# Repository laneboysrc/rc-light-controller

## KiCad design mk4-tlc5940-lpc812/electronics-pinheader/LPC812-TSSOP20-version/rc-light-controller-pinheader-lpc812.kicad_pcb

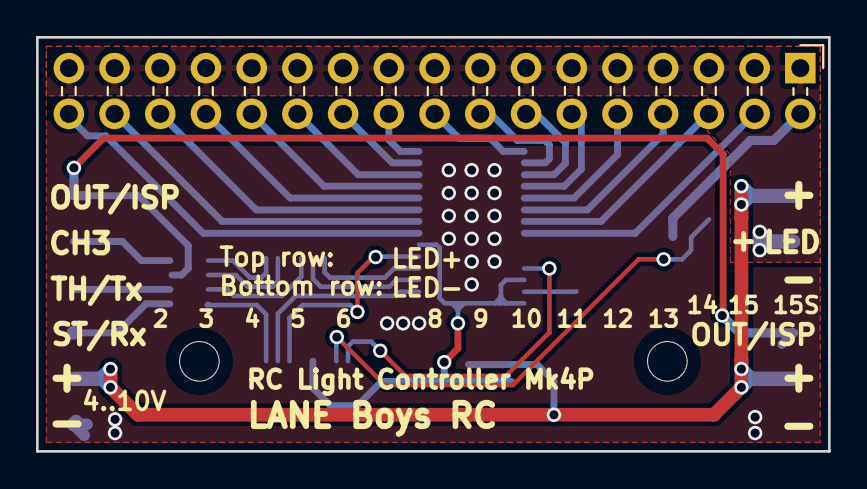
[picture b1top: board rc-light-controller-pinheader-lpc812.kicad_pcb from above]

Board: 2 copper layers, 44.0 x 23.0 mm, 14 parts (0 on the bottom side), 36 nets.

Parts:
C1: 1u/16V; C_0805_2012Metric
C2: 47u/6V3; C_0805_2012Metric
C3: 100n; C_0603_1608Metric
H1, H2: MountingHole; MountingHole_2.2mm_M2_ISO14580
J1: Pinheader right-angle 2x17; PinHeader_2x17_P2.54mm_Horizontal
J2, J3: Pinheader straight 1x06; PinHeader_1x06_P2.54mm_Flat
R1: 2k 1%; R_0603_1608Metric
RN1: 1k x4; R_Array_Convex_4x0603
T9: PMV30UN; SOT-23
U1: LPC812M101JDH20; TSSOP-20_4.4x6.5mm_P0.65mm
U2: TLC5940PWP; SOP65P640X120-29N
U3: MCP1703A-3302_SOT23; SOT-23W

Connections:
+3V3: C2.1, C3.1, U1.15, U2.6, U2.26, U2.28, U3.2
/BLANK: U1.18, U2.2
/CH3: RN1.5, U1.2
/CH3-in: J2.5, RN1.4
/GSCLK: U1.12, U2.25
/LED+: J1.1, J1.3, J1.5, J1.7, J1.9, J1.11, J1.13, J1.15, J1.17, J1.19, J1.21, J1.23, J1.25, J1.27, J1.29, J1.31, J1.33, J3.5
/OUT0: J1.34, U2.7
/OUT1: J1.32, U2.8
/OUT2: J1.30, U2.9
/OUT3: J1.28, U2.10
/OUT4: J1.26, U2.11
/OUT5: J1.24, U2.12
/OUT6: J1.22, U2.13
/OUT7: J1.20, U2.14
/OUT8: J1.18, U2.15
/OUT9: J1.16, U2.16
/OUT10: J1.14, U2.17
/OUT11: J1.12, U2.18
/OUT12: J1.10, U2.19
/OUT13: J1.8, U2.20
/OUT14: J1.6, U2.21
/OUT15: J1.4, U2.22
/OUT15S: T9.1, U1.13
/OUT15S_OUT: J1.2, T9.3
/OUT-ISP: RN1.6, U1.3
/OUT-ISP-out: J2.6, J3.3, RN1.3
/SCLK: U1.7, U2.4
/SIN: U1.17, U2.5
/ST-RX: RN1.8, U1.19
/ST-Rx-in: J2.3, RN1.1
/TH-TX: RN1.7, U1.5
/TH-Tx-in: J2.4, RN1.2
/VIN: C1.1, J2.2, J3.2, J3.6, U3.3
/XLAT: U1.6, U2.3
GND: C1.2, C2.2, C3.2, J2.1, J3.1, J3.4, R1.2, T9.2, U1.16, U2.1, U2.29, U3.1
unnamed: R1.1, U2.27

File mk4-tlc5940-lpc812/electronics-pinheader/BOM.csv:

Reference, Quantity, Value, Footprint, Datasheet
C1 ,1,"1u/16V","Capacitor_SMD:C_0805_2012Metric",""
C2 ,1,"47u/6V3","Capacitor_SMD:C_0805_2012Metric","https://www.vishay.com/doc?40189"
C3 ,1,"100n","Capacitor_SMD:C_0603_1608Metric","~"
H1 H2 ,2,"MountingHole","MountingHole:MountingHole_2.2mm_M2_ISO14580","~"
J1 ,1,"Pinheader right-angle 2x17","Connector_PinHeader_2.54mm:PinHeader_2x17_P2.54mm_Horizontal","~"
J2 J3 ,2,"Pinheader straight 1x06","rc-light-controller-tlc5940-lpc812:PinHeader_1x06_P2.54mm_Flat","~"
R1 ,1,"2k 1%","Resistor_SMD:R_0603_1608Metric","~"
RN1 ,1,"1k x4","Resistor_SMD:R_Array_Convex_4x0603","https://datasheet.lcsc.com/szlcsc/1810311812_UNI-ROYAL-Uniro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"
T9 ,1,"PMV30UN","Package_TO_SOT_SMD:SOT-23","https://assets.nexperia.com/documents/data-sheet/PMV30UN.pdf"
U1 ,1,"LPC812M101JDH20","Package_SO:TSSOP-20_4.4x6.5mm_P0.65mm","http://www.nxp.com/documents/data_sheet/LPC81XM.pdf"
U2 ,1,"TLC5940PWP","rc-light-controller-tlc5940-lpc812:SOP65P640X120-29N","http://www.ti.com/lit/ds/symlink/tlc5940.pdf"
U3 ,1,"MCP1703A-3302_SOT23","Package_TO_SOT_SMD:SOT-23W","http://ww1.microchip.com/downloads/en/DeviceDoc/20005122B.pdf"

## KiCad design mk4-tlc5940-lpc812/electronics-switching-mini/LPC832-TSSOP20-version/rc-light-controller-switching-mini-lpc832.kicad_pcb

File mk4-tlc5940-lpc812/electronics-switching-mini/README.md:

# Mk4S-mini - light controller with pin headers and 3 switching outputs

This is a new variant of the DIY RC Light Controller Mk4.
It has 3 (Mosfet) switched outputs on standard 2.54 mm pin headers.

This light controller is supposed to be used as "Slave" light controller in conjunction with an Mk4, Mk4P or Mk4S light controller. It is useful when more than one switched light output is required when using an Mk4 or Mk4P.

There are two circuit board designs available: one for the NXP LPC812 and one for LPC832 microcontroller, both in TSSOP-20 package.

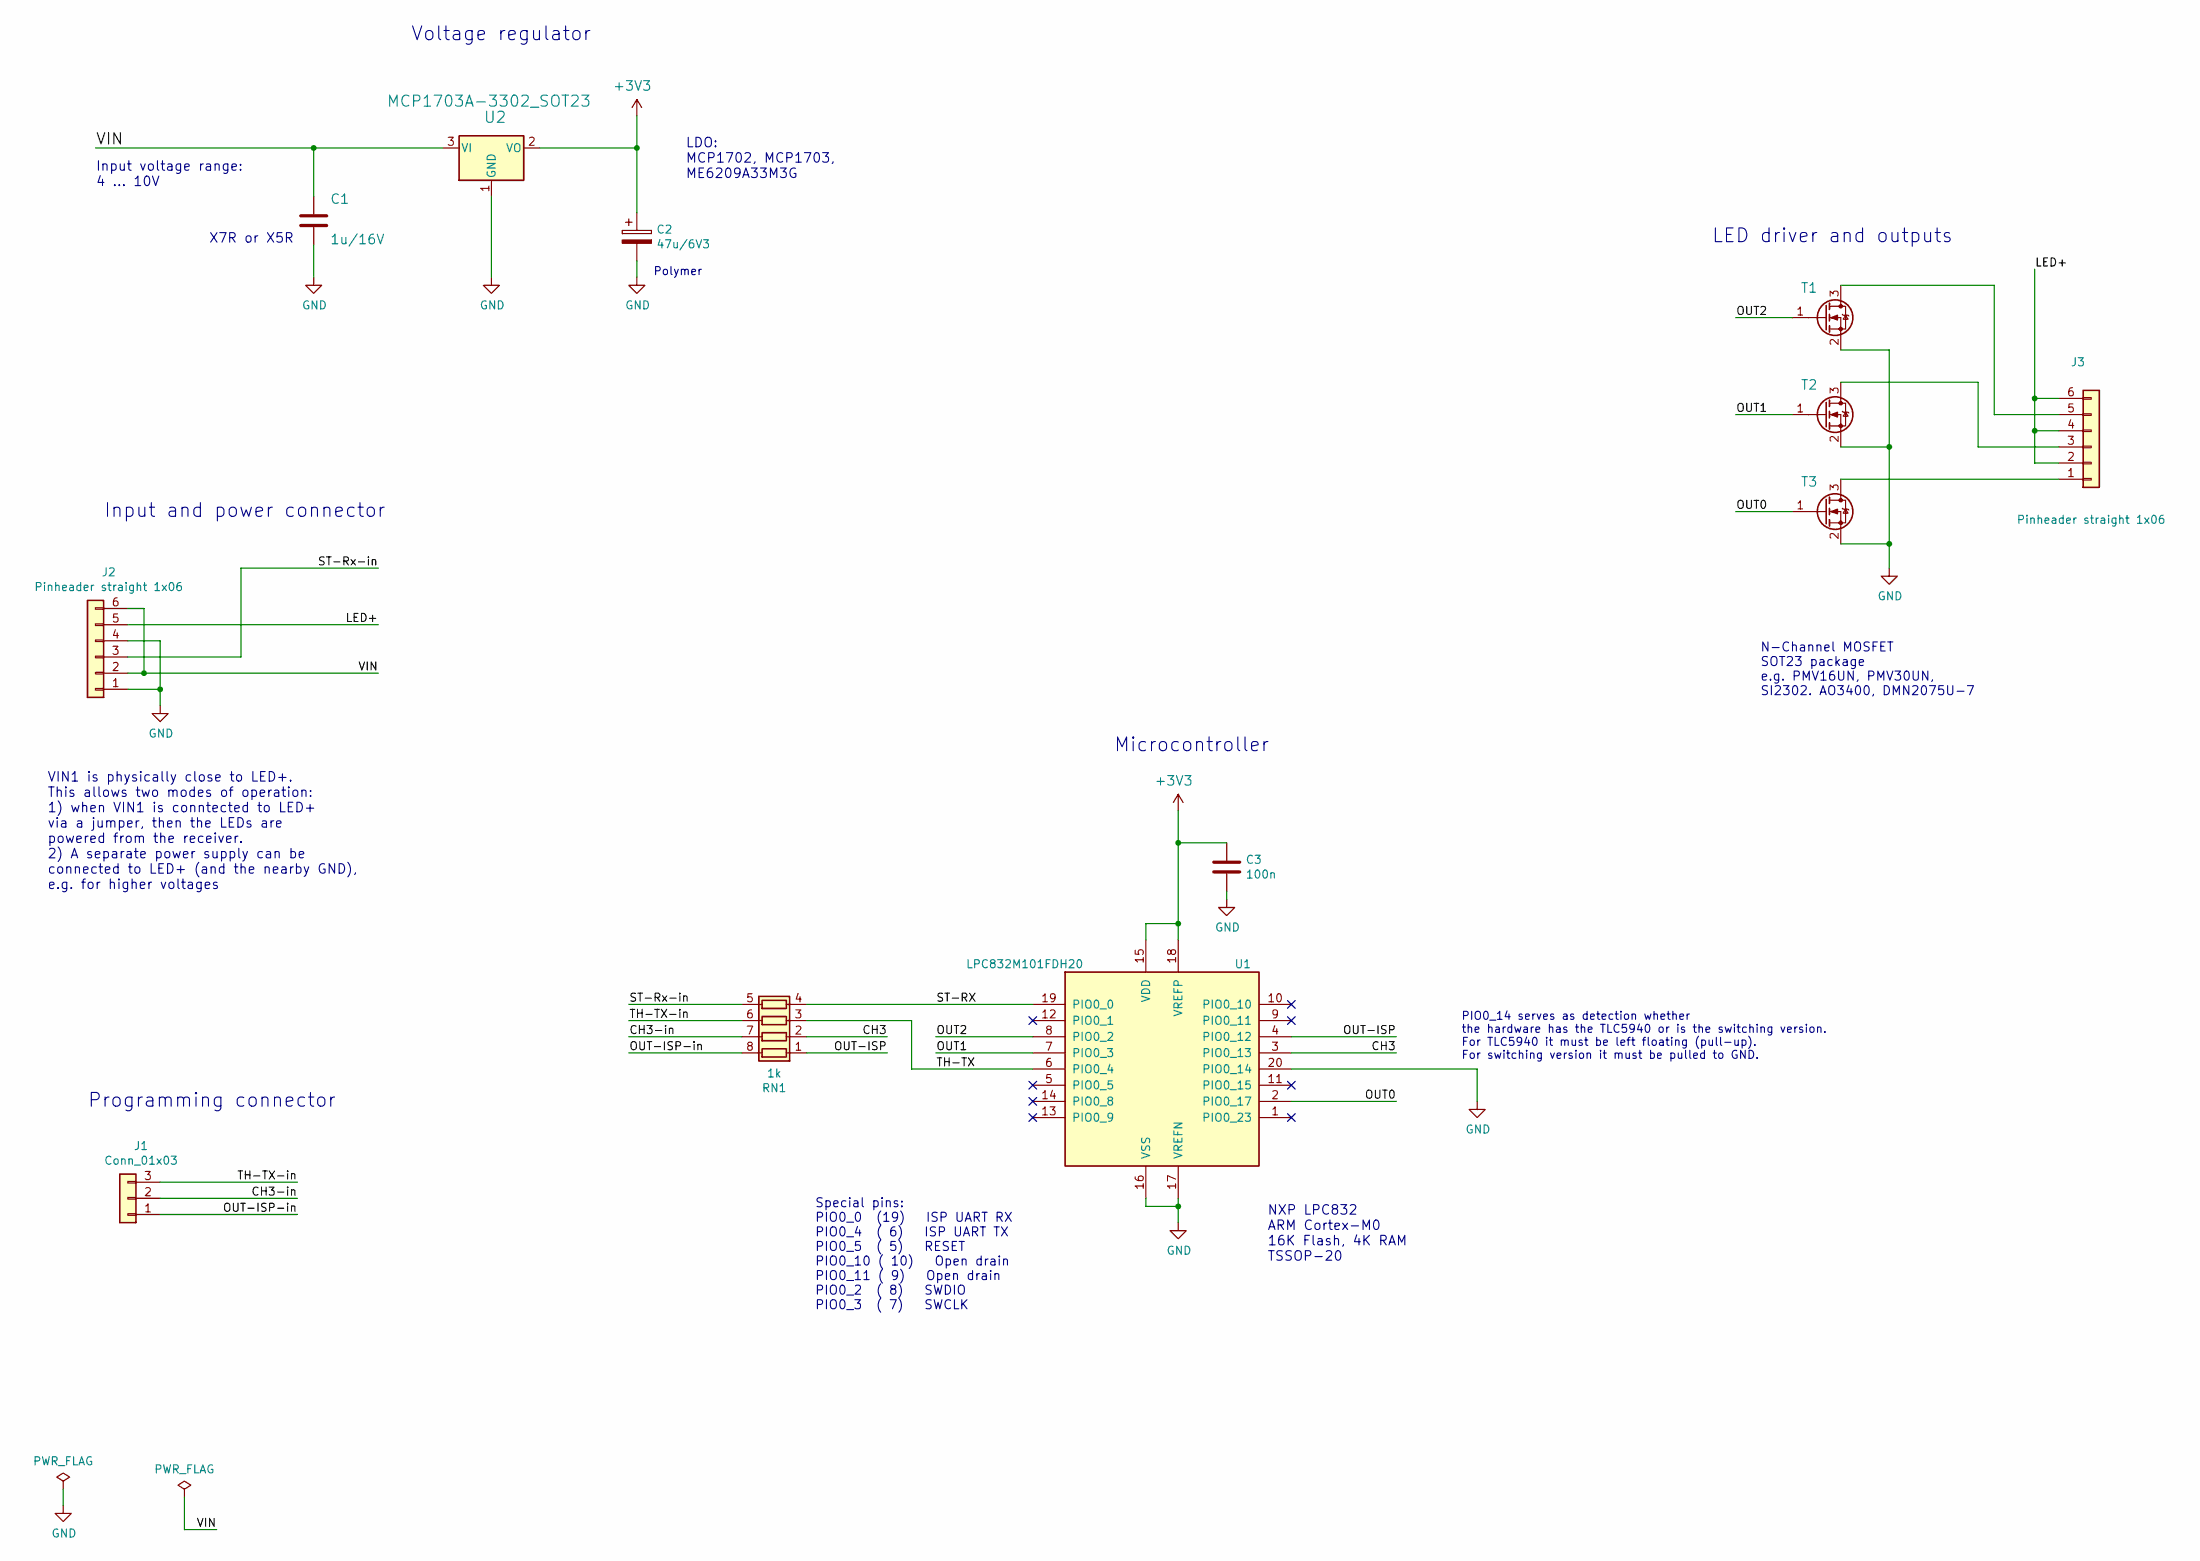
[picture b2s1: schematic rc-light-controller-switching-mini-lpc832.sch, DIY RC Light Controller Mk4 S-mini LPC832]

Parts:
C1: 1u/16V; C_0805_2012Metric
C2: 47u/6V3; C_0805_2012Metric
C3: 100n; C_0603_1608Metric
J1: Conn_01x03; PinHeader_1x03_P2.54mm_Vertical
J2, J3: Pinheader straight 1x06; PinHeader_1x06_P2.54mm_Flat
RN1: 1k; R_Array_Convex_4x0603
T1, T2, T3: PMV30UN; SOT-23
U1: LPC832M101FDH20; TSSOP-20_4.4x6.5mm_P0.65mm
U2: MCP1703A-3302_SOT23; SOT-23W

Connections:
+3V3: C2.1, C3.1, U1.15 (VDD), U1.18 (VREFP), U2.2 (VO)
/CH3: RN1.2 (R2.1), U1.3 (PIO0_13)
/CH3-in: J1.2, RN1.7 (R2.2)
/LED+: J2.5, J3.2, J3.4, J3.6
/OUT0: T3.1 (G), U1.2 (PIO0_17)
/OUT1: T2.1 (G), U1.7 (PIO0_3)
/OUT2: T1.1 (G), U1.8 (PIO0_2)
/OUT-ISP: RN1.1 (R1.1), U1.4 (PIO0_12)
/OUT-ISP-in: J1.1, RN1.8 (R1.2)
/ST-RX: RN1.4 (R4.1), U1.19 (PIO0_0)
/ST-Rx-in: J2.3, RN1.5 (R4.2)
/TH-TX: RN1.3 (R3.1), U1.6 (PIO0_4)
/TH-TX-in: J1.3, RN1.6 (R3.2)
/VIN: C1.1, J2.2, J2.6, U2.3 (VI)
GND: C1.2, C2.2, C3.2, J2.1, J2.4, T1.2 (S), T2.2 (S), T3.2 (S), U1.16 (VSS), U1.17 (VREFN), U1.20 (PIO0_14), U2.1 (GND)
unnamed: J3.1, T3.3 (D)
unnamed: J3.3, T2.3 (D)
unnamed: J3.5, T1.3 (D)

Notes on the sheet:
Special pins: PIO0_0 (19) ISP UART RX PIO0_4 ( 6) ISP UART TX PIO0_5 ( 5) RESET PIO0_10 ( 10) Open drain PIO0_11 ( 9) Open drain PIO0_2 ( 8) SWDIO PIO0_3 ( 7) SWCLK
Input and power connector
Voltage regulator
Microcontroller
X7R or X5R
Input voltage range: 4 ... 10V
LDO: MCP1702, MCP1703, ME6209A33M3G
N-Channel MOSFET SOT23 package e.g. PMV16UN, PMV30UN, SI2302. AO3400, DMN2075U-7
Polymer
LED driver and outputs
VIN1 is physically close to LED+. This allows two modes of operation: 1) when VIN1 is conntected to LED+ via a jumper, then the LEDs are powered from the receiver. 2) A separate power supply can be connected to LED+ (and the nearby GND), e.g. for higher voltages
PIO0_14 serves as detection whether the hardware has the TLC5940 or is the switching version. For TLC5940 it must be left floating (pull-up). For switching version it must be pulled to GND.
Programming connector
NXP LPC832 ARM Cortex-M0 16K Flash, 4K RAM TSSOP-20

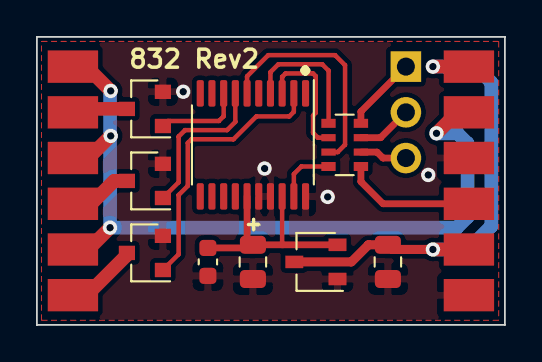
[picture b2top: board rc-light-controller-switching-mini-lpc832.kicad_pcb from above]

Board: 2 copper layers, 26.0 x 16.0 mm, 12 parts (0 on the bottom side), 18 nets.

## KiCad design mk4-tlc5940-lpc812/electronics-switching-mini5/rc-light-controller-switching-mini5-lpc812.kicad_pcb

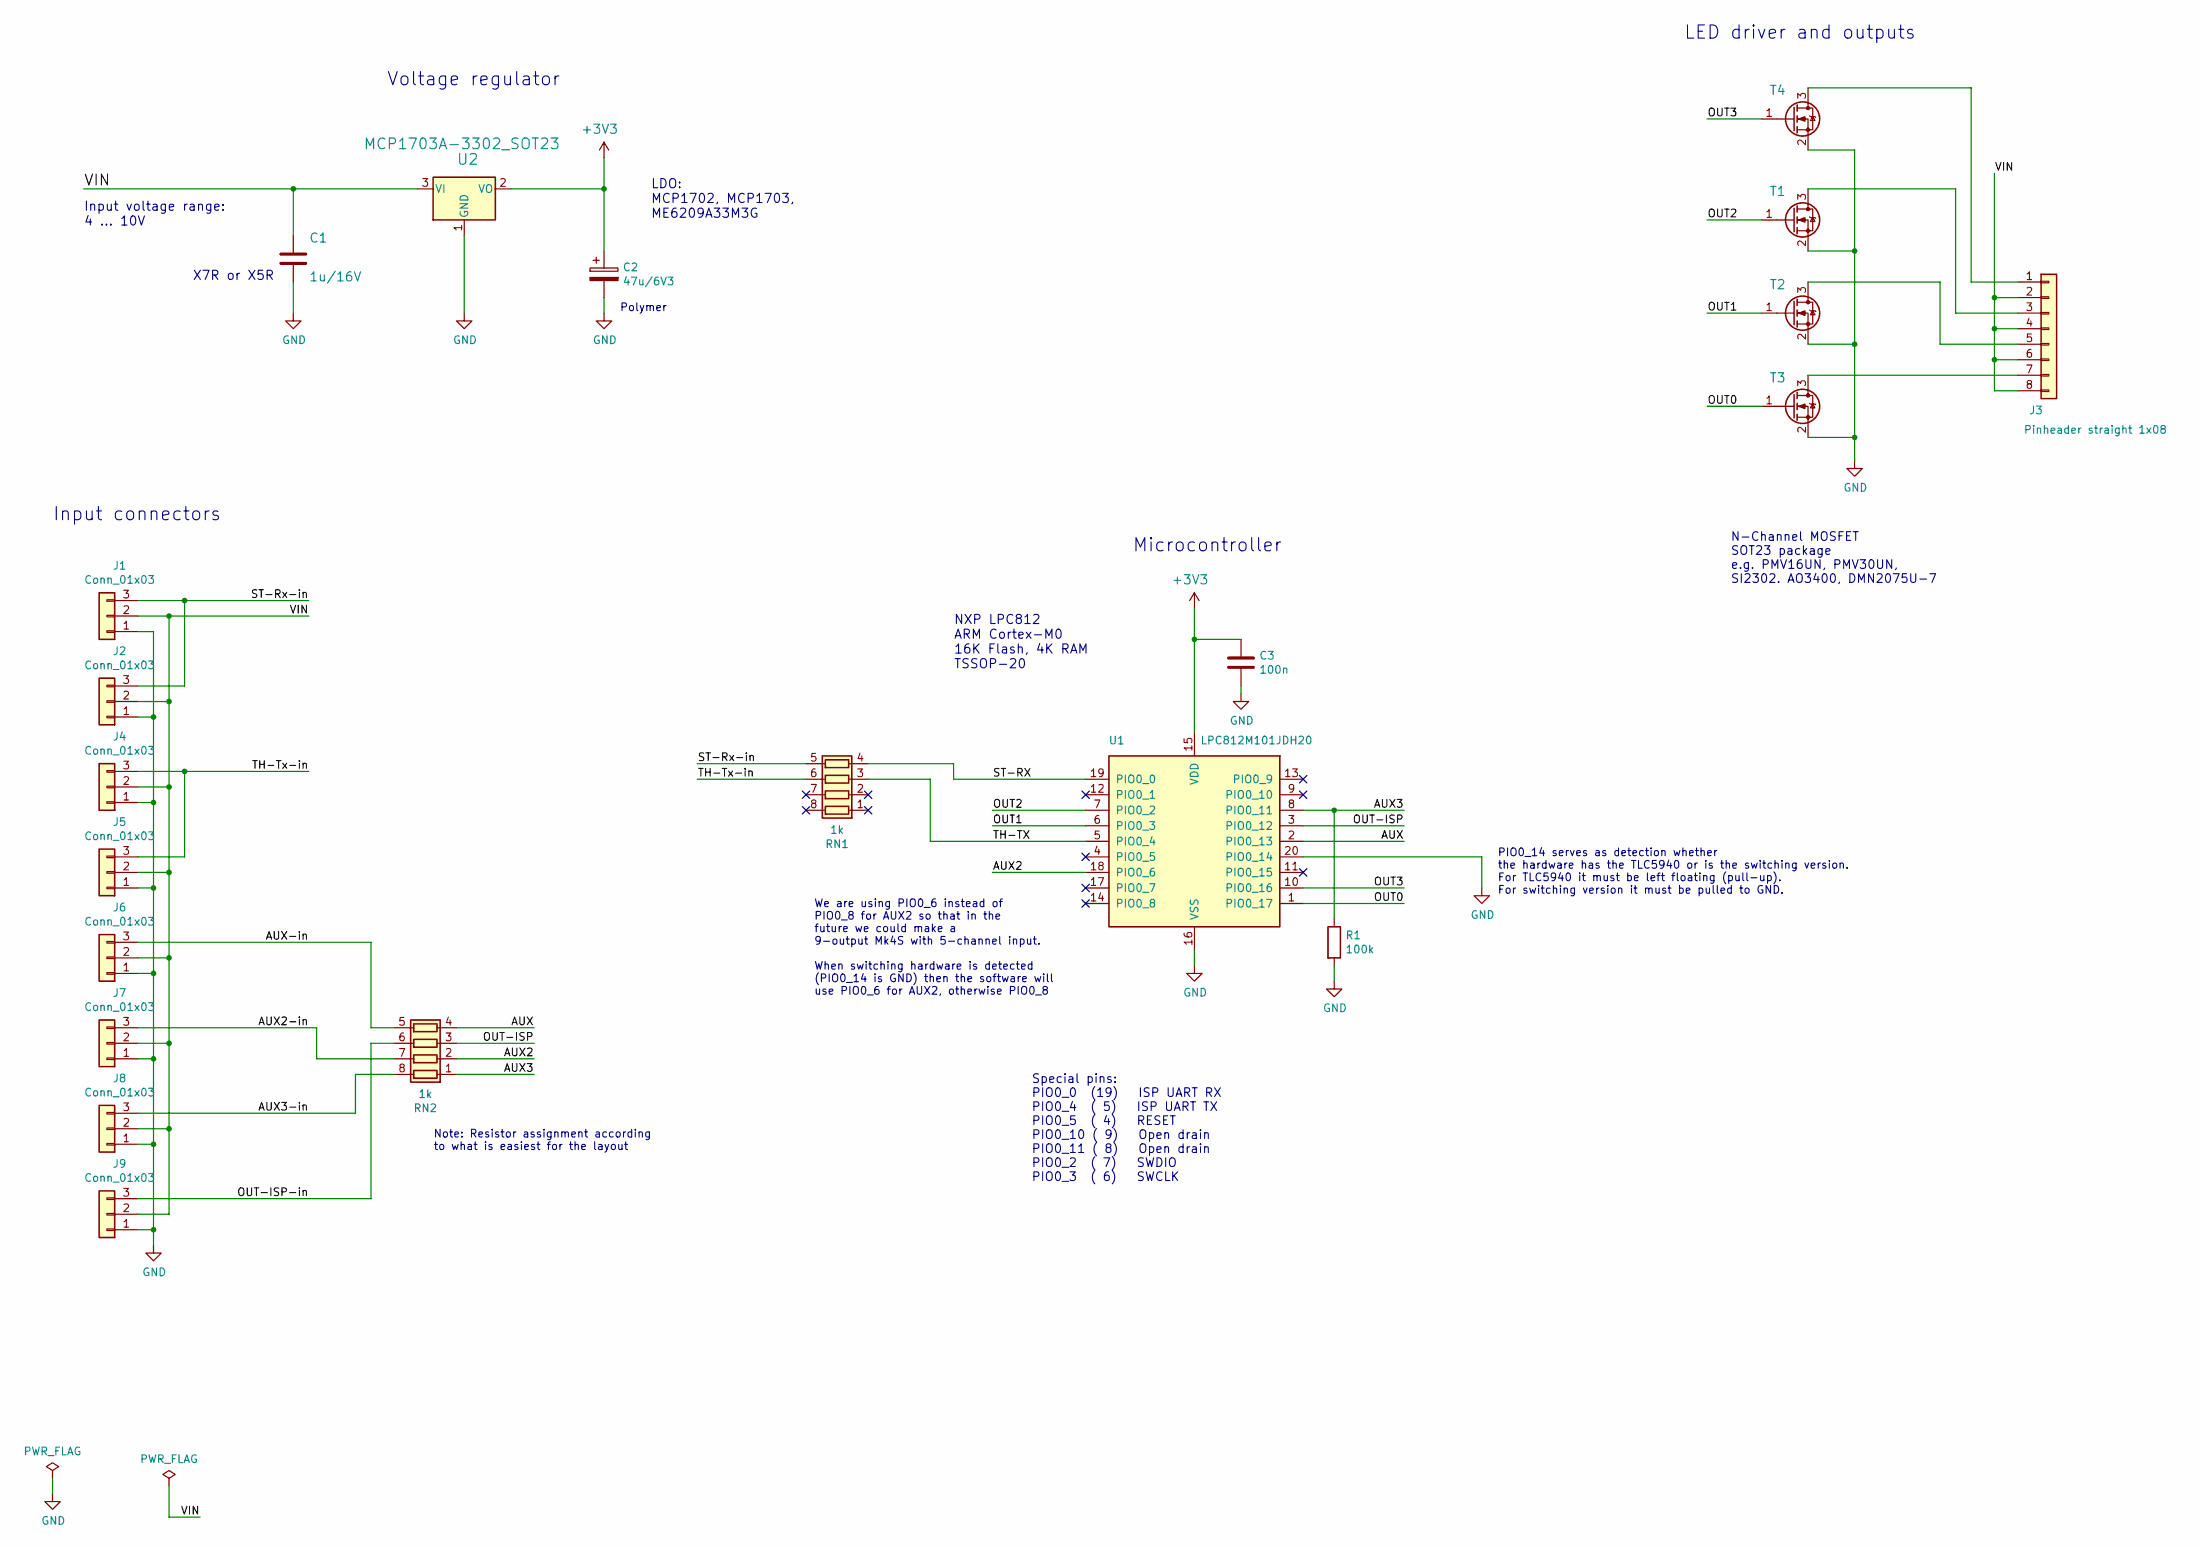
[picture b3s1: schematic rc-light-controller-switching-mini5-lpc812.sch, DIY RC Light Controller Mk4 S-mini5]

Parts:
C1: 1u/16V; C_0805_2012Metric
C2: 47u/6V3; C_0805_2012Metric
C3: 100n; C_0603_1608Metric
J1, J2, J4, J5, J6, J7, J8, J9: Conn_01x03; PinHeader_1x03_P2.54mm_Vertical_nosilk
J3: Pinheader straight 1x08; PinHeader_1x08_P2.54mm_Vertical_nosilk
R1: 100k; R_0603_1608Metric
RN1, RN2: 1k; R_Array_Convex_4x0603
T1, T2, T3, T4: PMV30UN; SOT-23
U1: LPC812M101JDH20; TSSOP-20_4.4x6.5mm_P0.65mm
U2: MCP1703A-3302_SOT23; SOT-23W

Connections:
+3V3: C2.1, C3.1, U1.15 (VDD), U2.2 (VO)
/AUX: RN2.4 (R4.1), U1.2 (PIO0_13)
/AUX2: RN2.2 (R2.1), U1.18 (PIO0_6)
/AUX2-in: J7.3, RN2.7 (R2.2)
/AUX3: R1.1, RN2.1 (R1.1), U1.8 (PIO0_11)
/AUX3-in: J8.3, RN2.8 (R1.2)
/AUX-in: J6.3, RN2.5 (R4.2)
/OUT0: T3.1 (G), U1.1 (PIO0_17)
/OUT1: T2.1 (G), U1.6 (PIO0_3)
/OUT2: T1.1 (G), U1.7 (PIO0_2)
/OUT3: T4.1 (G), U1.10 (PIO0_16)
/OUT-ISP: RN2.3 (R3.1), U1.3 (PIO0_12)
/OUT-ISP-in: J9.3, RN2.6 (R3.2)
/ST-RX: RN1.4 (R4.1), U1.19 (PIO0_0)
/ST-Rx-in: J1.3, J2.3, RN1.5 (R4.2)
/TH-TX: RN1.3 (R3.1), U1.5 (PIO0_4)
/TH-Tx-in: J4.3, J5.3, RN1.6 (R3.2)
/VIN: C1.1, J1.2, J2.2, J3.2, J3.4, J3.6, J3.8, J4.2, J5.2, J6.2, J7.2, J8.2, J9.2, U2.3 (VI)
GND: C1.2, C2.2, C3.2, J1.1, J2.1, J4.1, J5.1, J6.1, J7.1, J8.1, J9.1, R1.2, T1.2 (S), T2.2 (S), T3.2 (S), T4.2 (S), U1.16 (VSS), U1.20 (PIO0_14), U2.1 (GND)
unnamed: J3.1, T4.3 (D)
unnamed: J3.3, T1.3 (D)
unnamed: J3.5, T2.3 (D)
unnamed: J3.7, T3.3 (D)

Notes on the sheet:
Special pins: PIO0_0 (19) ISP UART RX PIO0_4 ( 5) ISP UART TX PIO0_5 ( 4) RESET PIO0_10 ( 9) Open drain PIO0_11 ( 8) Open drain PIO0_2 ( 7) SWDIO PIO0_3 ( 6) SWCLK
Input connectors
Voltage regulator
Microcontroller
X7R or X5R
Input voltage range: 4 ... 10V
LDO: MCP1702, MCP1703, ME6209A33M3G
NXP LPC812 ARM Cortex-M0 16K Flash, 4K RAM TSSOP-20
N-Channel MOSFET SOT23 package e.g. PMV16UN, PMV30UN, SI2302. AO3400, DMN2075U-7
Polymer
LED driver and outputs
PIO0_14 serves as detection whether the hardware has the TLC5940 or is the switching version. For TLC5940 it must be left floating (pull-up). For switching version it must be pulled to GND.
We are using PIO0_6 instead of PIO0_8 for AUX2 so that in the future we could make a 9-output Mk4S with 5-channel input. When switching hardware is detected (PIO0_14 is GND) then the software will use PIO0_6 for AUX2, otherwise PIO0_8
Note: Resistor assignment according to what is easiest for the layout

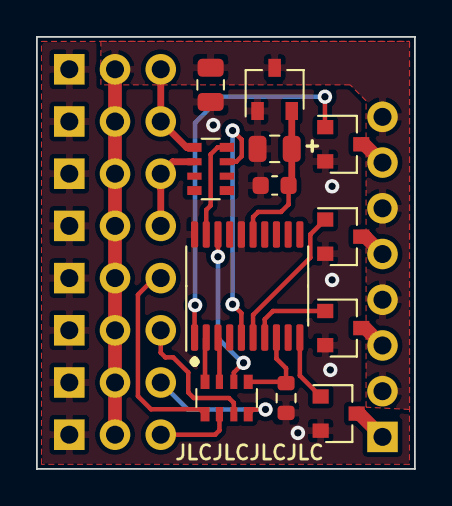
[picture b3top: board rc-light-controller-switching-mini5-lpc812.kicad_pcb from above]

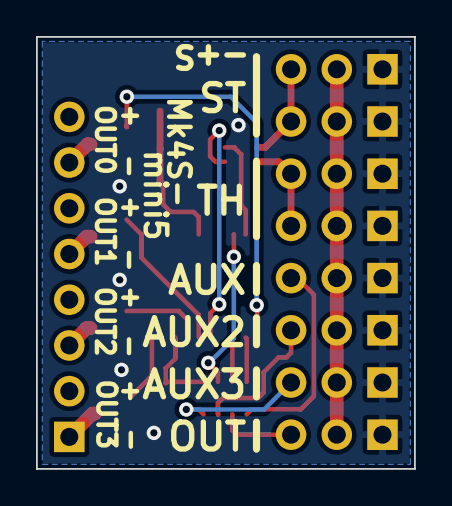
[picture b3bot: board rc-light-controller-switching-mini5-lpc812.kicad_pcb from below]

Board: 2 copper layers, 21.0 x 24.0 mm, 21 parts (9 on the bottom side), 23 nets.

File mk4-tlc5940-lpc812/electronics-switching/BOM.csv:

Reference, Quantity, Value, Footprint, Datasheet
C1 ,1,"1u/16V","Capacitor_SMD:C_0805_2012Metric",""
C2 ,1,"47u/6V3","Capacitor_SMD:C_0805_2012Metric","https://www.vishay.com/doc?40189"
C3 ,1,"100n","Capacitor_SMD:C_0603_1608Metric","~"
H1 H2 ,2,"MountingHole","MountingHole:MountingHole_2.2mm_M2_ISO14580","~"
J1 ,1,"Pinheader right-angle 2x17","Connector_PinHeader_2.54mm:PinHeader_2x17_P2.54mm_Horizontal","~"
J2 J3 ,2,"Pinheader straight 1x06","rc-light-controller-tlc5940-lpc812:PinHeader_1x06_P2.54mm_Flat","~"
RN1 ,1,"1k x4","Resistor_SMD:R_Array_Convex_4x0603","https://datasheet.lcsc.com/szlcsc/1810311812_UNI-ROYAL-Uniro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"
T1 T2 T3 T4 T5 T6 T7 T9 T8 ,9,"PMV30UN","Package_TO_SOT_SMD:SOT-23","https://assets.nexperia.com/documents/data-sheet/PMV30UN.pdf"
U1 ,1,"LPC812M101JDH20","Package_SO:TSSOP-20_4.4x6.5mm_P0.65mm","http://www.nxp.com/documents/data_sheet/LPC81XM.pdf"
U2 ,1,"3V3","Package_TO_SOT_SMD:SOT-23W",""

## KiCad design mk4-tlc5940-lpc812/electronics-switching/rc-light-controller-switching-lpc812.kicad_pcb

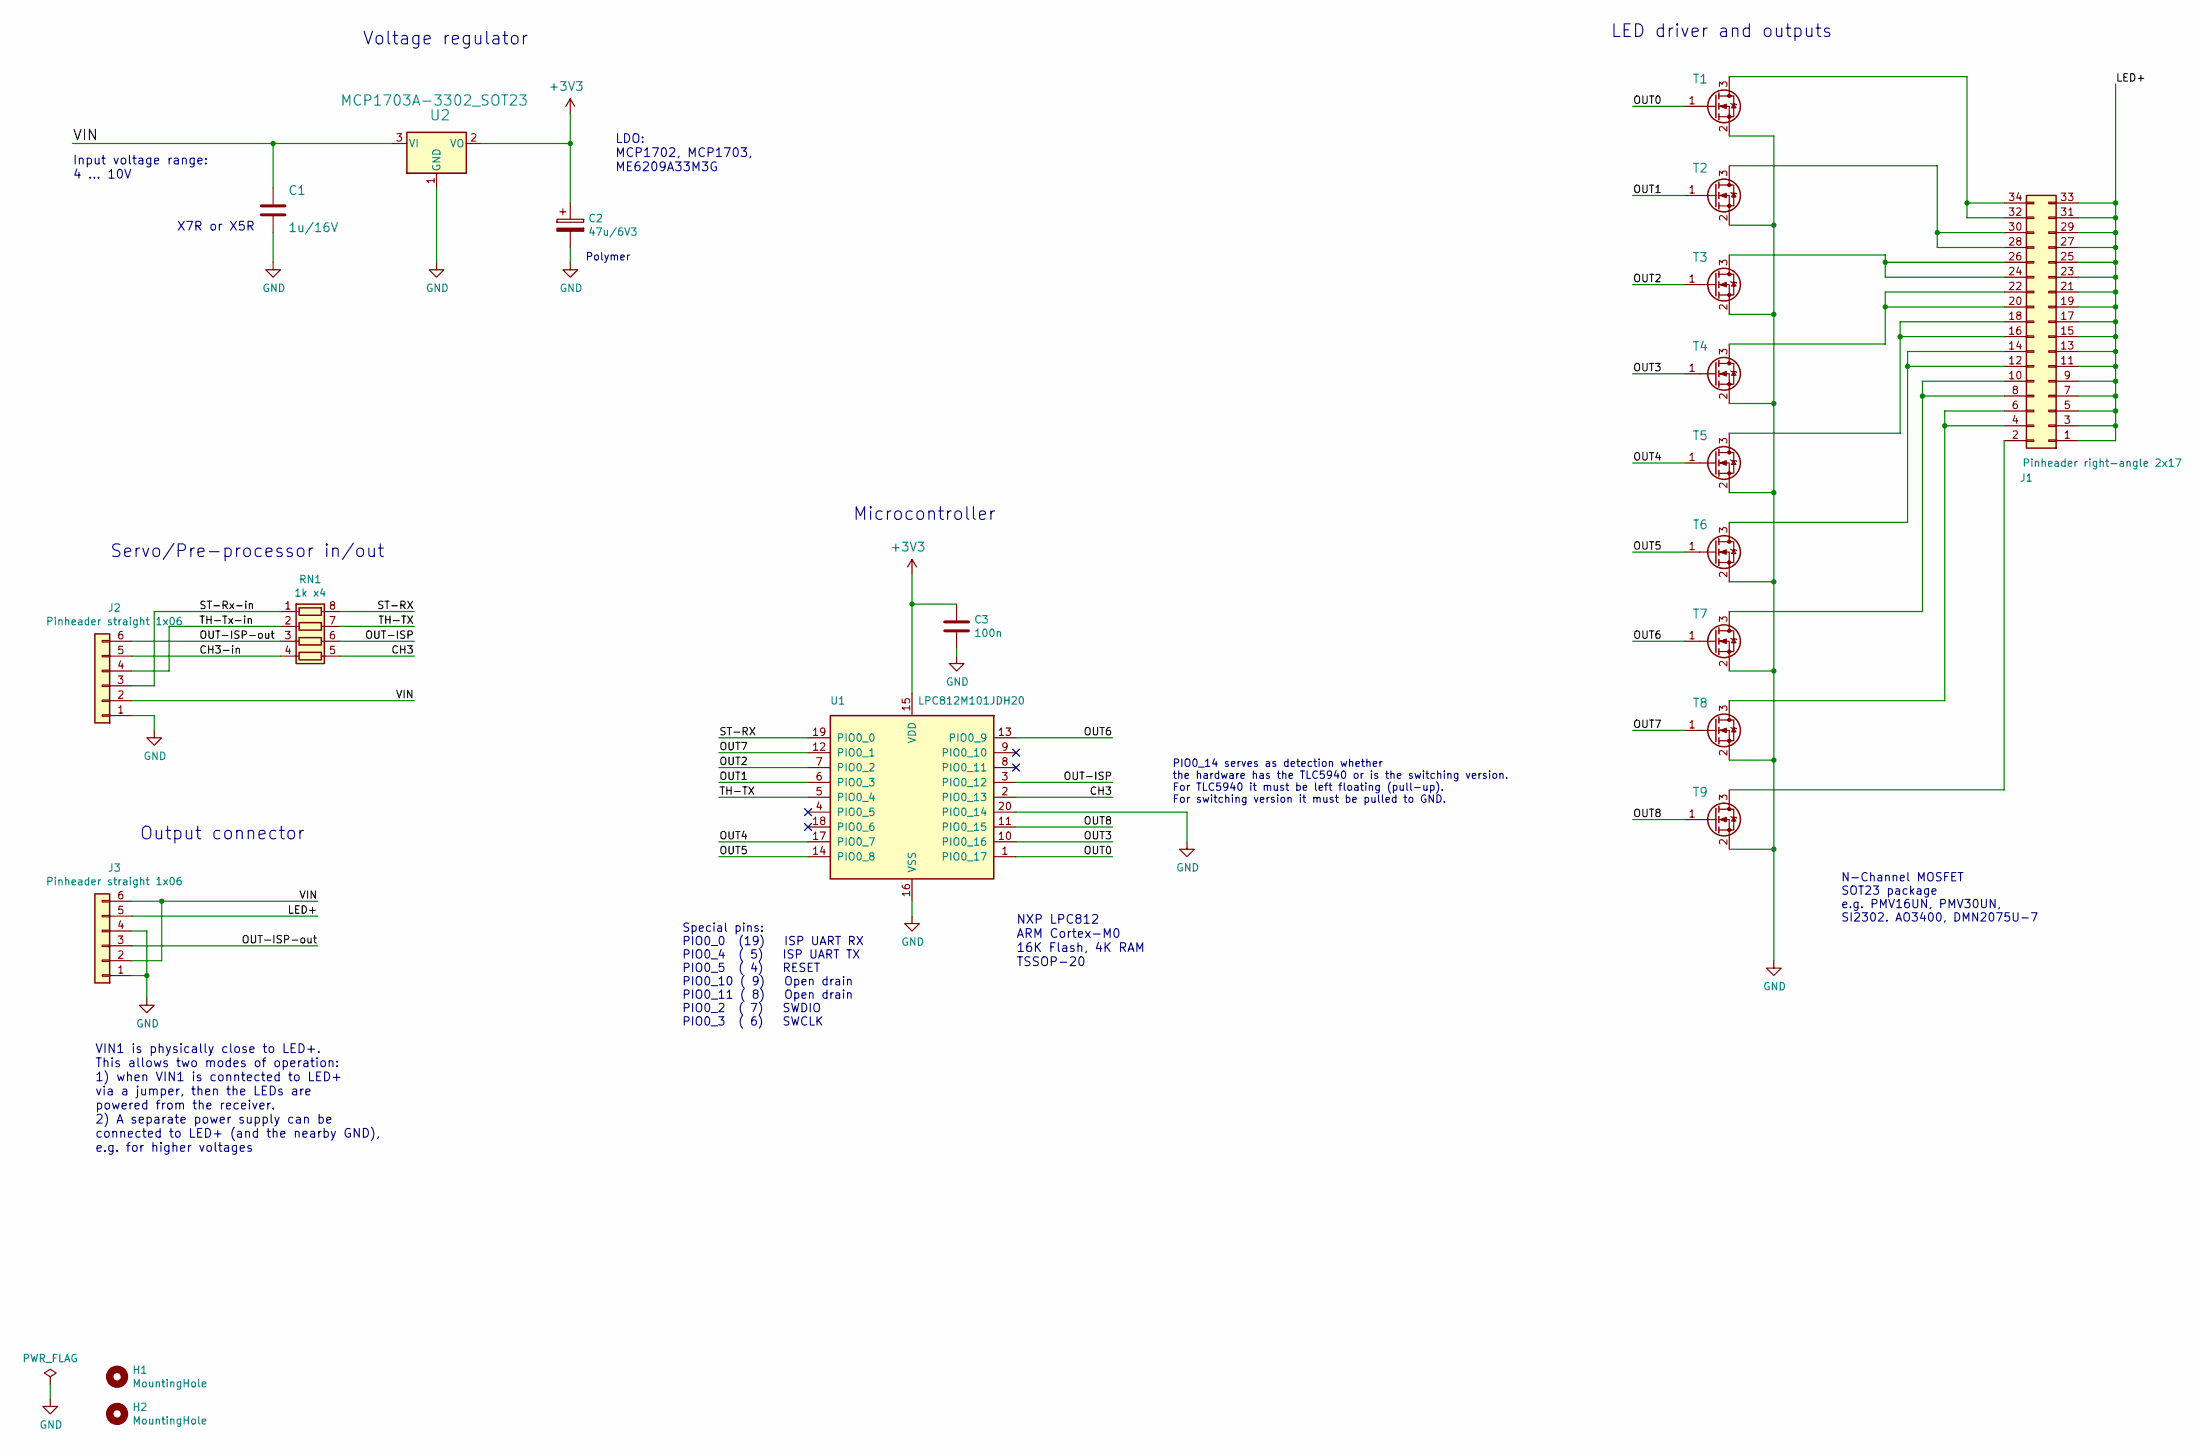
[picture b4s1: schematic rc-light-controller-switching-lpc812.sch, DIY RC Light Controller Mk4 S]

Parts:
C1: 1u/16V; C_0805_2012Metric
C2: 47u/6V3; C_0805_2012Metric
C3: 100n; C_0603_1608Metric
H1, H2: MountingHole; MountingHole_2.2mm_M2_ISO14580
J1: Pinheader right-angle 2x17; PinHeader_2x17_P2.54mm_Horizontal
J2, J3: Pinheader straight 1x06; PinHeader_1x06_P2.54mm_Flat
RN1: 1k x4; R_Array_Convex_4x0603
T1, T2, T3, T4, T5, T6, T7, T8, T9: PMV30UN; SOT-23
U1: LPC812M101JDH20; TSSOP-20_4.4x6.5mm_P0.65mm
U2: MCP1703A-3302_SOT23; SOT-23W

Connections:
+3V3: C2.1, C3.1, U1.15 (VDD), U2.2 (VO)
/CH3: RN1.5 (R4.2), U1.2 (PIO0_13)
/CH3-in: J2.5, RN1.4 (R4.1)
/LED+: J1.1, J1.3, J1.5, J1.7, J1.9, J1.11, J1.13, J1.15, J1.17, J1.19, J1.21, J1.23, J1.25, J1.27, J1.29, J1.31, J1.33, J3.5
/OUT0: T1.1 (G), U1.1 (PIO0_17)
/OUT1: T2.1 (G), U1.6 (PIO0_3)
/OUT2: T3.1 (G), U1.7 (PIO0_2)
/OUT3: T4.1 (G), U1.10 (PIO0_16)
/OUT4: T5.1 (G), U1.17 (PIO0_7)
/OUT5: T6.1 (G), U1.14 (PIO0_8)
/OUT6: T7.1 (G), U1.13 (PIO0_9)
/OUT7: T8.1 (G), U1.12 (PIO0_1)
/OUT15S: T9.1 (G), U1.11 (PIO0_15)
/OUT-ISP: RN1.6 (R3.2), U1.3 (PIO0_12)
/OUT-ISP-out: J2.6, J3.3, RN1.3 (R3.1)
/ST-RX: RN1.8 (R1.2), U1.19 (PIO0_0)
/ST-Rx-in: J2.3, RN1.1 (R1.1)
/TH-TX: RN1.7 (R2.2), U1.5 (PIO0_4)
/TH-Tx-in: J2.4, RN1.2 (R2.1)
/VIN: C1.1, J2.2, J3.2, J3.6, U2.3 (VI)
GND: C1.2, C2.2, C3.2, J2.1, J3.1, J3.4, T1.2 (S), T2.2 (S), T3.2 (S), T4.2 (S), T5.2 (S), T6.2 (S), T7.2 (S), T8.2 (S), T9.2 (S), U1.16 (VSS), U1.20 (PIO0_14), U2.1 (GND)
unnamed: J1.2, T9.3 (D)
unnamed: J1.4, J1.6, T8.3 (D)
unnamed: J1.8, J1.10, T7.3 (D)
unnamed: J1.12, J1.14, T6.3 (D)
unnamed: J1.16, J1.18, T5.3 (D)
unnamed: J1.20, J1.22, T4.3 (D)
unnamed: J1.24, J1.26, T3.3 (D)
unnamed: J1.28, J1.30, T2.3 (D)
unnamed: J1.32, J1.34, T1.3 (D)

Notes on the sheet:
Special pins: PIO0_0 (19) ISP UART RX PIO0_4 ( 5) ISP UART TX PIO0_5 ( 4) RESET PIO0_10 ( 9) Open drain PIO0_11 ( 8) Open drain PIO0_2 ( 7) SWDIO PIO0_3 ( 6) SWCLK
Servo/Pre-processor in/out
Voltage regulator
Microcontroller
X7R or X5R
Input voltage range: 4 ... 10V
LDO: MCP1702, MCP1703, ME6209A33M3G
NXP LPC812 ARM Cortex-M0 16K Flash, 4K RAM TSSOP-20
N-Channel MOSFET SOT23 package e.g. PMV16UN, PMV30UN, SI2302. AO3400, DMN2075U-7
Polymer
LED driver and outputs
VIN1 is physically close to LED+. This allows two modes of operation: 1) when VIN1 is conntected to LED+ via a jumper, then the LEDs are powered from the receiver. 2) A separate power supply can be connected to LED+ (and the nearby GND), e.g. for higher voltages
Output connector
PIO0_14 serves as detection whether the hardware has the TLC5940 or is the switching version. For TLC5940 it must be left floating (pull-up). For switching version it must be pulled to GND.

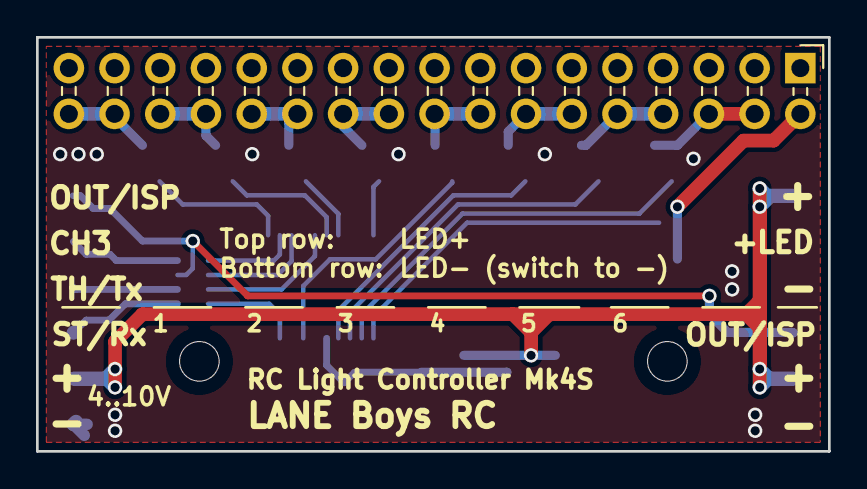
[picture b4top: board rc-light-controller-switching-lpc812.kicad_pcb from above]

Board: 2 copper layers, 44.0 x 23.0 mm, 20 parts (0 on the bottom side), 30 nets.

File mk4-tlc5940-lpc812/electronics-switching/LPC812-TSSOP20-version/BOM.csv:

Reference, Quantity, Value, Footprint, Datasheet
C1 ,1,"1u/16V","Capacitor_SMD:C_0805_2012Metric",""
C2 ,1,"47u/6V3","Capacitor_SMD:C_0805_2012Metric","https://www.vishay.com/doc?40189"
C3 ,1,"100n","Capacitor_SMD:C_0603_1608Metric","~"
H1 H2 ,2,"MountingHole","MountingHole:MountingHole_2.2mm_M2_ISO14580","~"
J1 ,1,"Pinheader right-angle 2x17","Connector_PinHeader_2.54mm:PinHeader_2x17_P2.54mm_Horizontal","~"
J2 J3 ,2,"Pinheader straight 1x06","rc-light-controller-tlc5940-lpc812:PinHeader_1x06_P2.54mm_Flat","~"
RN1 ,1,"1k x4","Resistor_SMD:R_Array_Convex_4x0603","https://datasheet.lcsc.com/szlcsc/1810311812_UNI-ROYAL-Uniro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"
T1 T2 T3 T4 T5 T6 T7 T9 T8 ,9,"PMV30UN","Package_TO_SOT_SMD:SOT-23","https://assets.nexperia.com/documents/data-sheet/PMV30UN.pdf"
U1 ,1,"LPC812M101JDH20","Package_SO:TSSOP-20_4.4x6.5mm_P0.65mm","http://www.nxp.com/documents/data_sheet/LPC81XM.pdf"
U2 ,1,"MCP1703A-3302","Package_TO_SOT_SMD:SOT-23W",""

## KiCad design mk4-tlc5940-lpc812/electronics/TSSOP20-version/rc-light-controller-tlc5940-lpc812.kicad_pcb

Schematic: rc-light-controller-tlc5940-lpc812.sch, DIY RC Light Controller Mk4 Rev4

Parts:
C1: 1u/16V; C_0805_2012Metric
C2: 47u/6V3; C_0805_2012Metric
C3: 100n; C_0603_1608Metric
LED+1, LED+2: SMD50X100
OUT0, OUT1, OUT2, OUT3, OUT4, OUT5, OUT6, OUT7, OUT8, OUT9, OUT10, OUT11, OUT12, OUT13, OUT14, OUT15, OUT15S1: SMD50X100
PAD1: +; SMD80X120
PAD2: -; SMD80X120
PAD3: ST/Rx; SMD80X120
PAD4: TH/Tx; SMD80X120
PAD5: CH3; SMD80X120
PAD6: OUT/ISP; SMD80X120
R1: 2k0=20mA; R_0603_1608Metric
R2, R3, R4, R5: 1k; R_0603_1608Metric
T1: NMOSSOT23; SOT-23
U1: 3V3; SOT-23W
U2: LPC812M101JDH20; TSSOP-20_4.4x6.5mm_P0.65mm
U3: TLC5940PWP; SOP65P640X120-29N

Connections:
+3V3: C2.1, C3.2, U1.2, U2.15, U3.6, U3.26, U3.28
/AUX: R3.1, U2.2
/AUX-IN: PAD5.1, R3.2
/BLANK: U2.18, U3.2
/GSCLK: U2.12, U3.25
/IREF: R1.1, U3.27
/OUT0: OUT0.1, U3.7
/OUT1: OUT1.1, U3.8
/OUT2: OUT2.1, U3.9
/OUT3: OUT3.1, U3.10
/OUT4: OUT4.1, U3.11
/OUT5: OUT5.1, U3.12
/OUT6: OUT6.1, U3.13
/OUT7: OUT7.1, U3.14
/OUT8: OUT8.1, U3.15
/OUT9: OUT9.1, U3.16
/OUT10: OUT10.1, U3.17
/OUT11: OUT11.1, U3.18
/OUT12: OUT12.1, U3.19
/OUT13: OUT13.1, U3.20
/OUT14: OUT14.1, U3.21
/OUT15: OUT15.1, U3.22
/OUT15S: OUT15S1.1, T1.3
/OUT-ISP: R4.1, U2.3
/OUT-ISP-OUT: PAD6.1, R4.2
/OUT-SWITCHED: T1.1, U2.13
/SCLK: U2.7, U3.4
/SIN: U2.17, U3.5
/ST-IN: PAD3.1, R2.2
/ST-RX: R2.1, U2.19
/TH-IN: PAD4.1, R5.2
/TH-TX: R5.1, U2.5
/VIN: C1.1, LED+1.1, LED+2.1, PAD1.1, U1.3
/XLAT: U2.6, U3.3
GND: C1.2, C2.2, C3.1, PAD2.1, R1.2, T1.2, U1.1, U2.16, U3.1, U3.29

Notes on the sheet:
Special pins: PIO0_0 (16) ISP UART RX PIO0_4 ( 4) ISP UART TX PIO0_5 ( 3) RESET PIO0_10 ( 8) Open drain PIO0_11 ( 7) Open drain PIO0_2 ( 6) SWDIO PIO0_3 ( 5) SWCLK
Servo in/out
LED driver and outputs
Voltage regulator
Microcontroller
X7R
Input voltage range: 4 ... 10V
LDO: Microchip MCP1702 or MCP1703
X5R or X7R
NXP LPC812 ARM Cortex-M0 16K Flash, 4K RAM TSSOP-20
Switched output for light bar or similar
N-Channel MOSFET SOT23 package e.g. NXP PMV16UN
Polymer

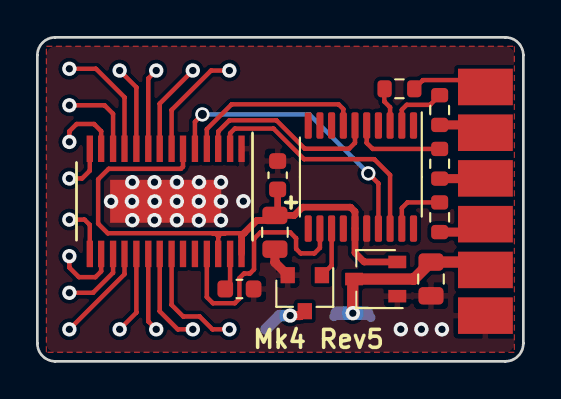
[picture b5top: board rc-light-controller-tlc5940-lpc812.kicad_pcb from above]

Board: 2 copper layers, 27.0 x 18.0 mm, 37 parts (0 on the bottom side), 35 nets.
